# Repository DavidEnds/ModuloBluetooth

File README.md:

# ModuloBluetooth
This module enables any Arduino board to communicate data over Bluetooth. It's a great solution if you want to create wireless projects ranging from robots to living room lamps.

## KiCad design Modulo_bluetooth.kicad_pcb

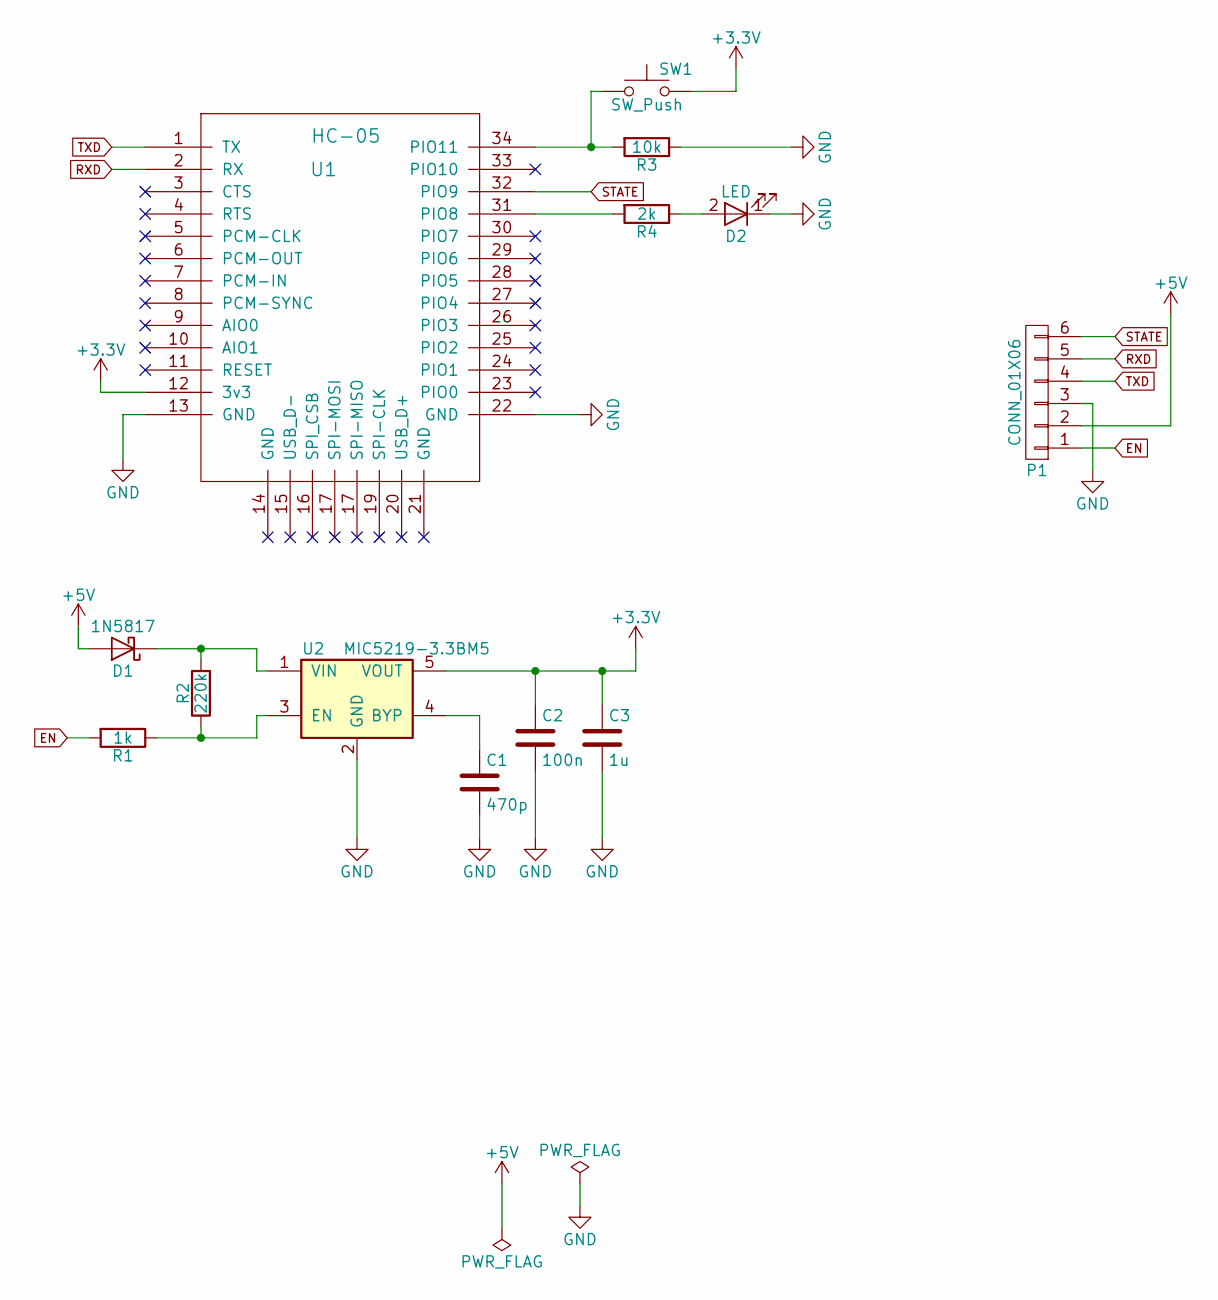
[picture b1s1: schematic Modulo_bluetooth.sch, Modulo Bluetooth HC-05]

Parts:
C1: 470p; C_0805_HandSoldering
C2: 100n; C_0805_HandSoldering
C3: 1u; C_0805_HandSoldering
D1: 1N5817; do214ac
D2: LED; LED_0805
P1: CONN_01X06; Pin_Header_Angled_1x06
R1: 1k; R_0805_HandSoldering
R2: 220k; R_0805_HandSoldering
R3: 10k; R_0805_HandSoldering
R4: 2k; R_0805_HandSoldering
SW1: SW_Push; SW_SPST_B3U-1000P-B
U1: HC-05; HC-06
U2: MIC5219-3.3BM5; SOT-23-5

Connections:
+3V3: C2.1, C3.1, SW1.2, U1.12 (3v3), U2.5 (VOUT)
+5V: D1.2 (A), P1.2
EN: P1.1, R1.2
GND: C1.2, C2.2, C3.2, D2.1 (K), P1.3, R3.1, U1.13 (GND), U1.22 (GND), U2.2 (GND)
unnamed: C1.1, U2.4 (BYP)
unnamed: D1.1 (K), R2.2, U2.1 (VIN)
unnamed: D2.2 (A), R4.1
unnamed: R1.1, R2.1, U2.3 (EN)
unnamed: R3.2, SW1.1, U1.34 (PIO11)
unnamed: R4.2, U1.31 (PIO8)
RXD: P1.5, U1.2 (RX)
STATE: P1.6, U1.32 (PIO9)
TXD: P1.4, U1.1 (TX)

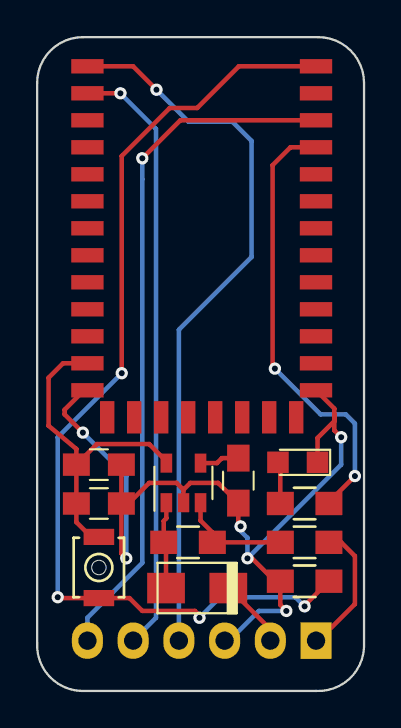
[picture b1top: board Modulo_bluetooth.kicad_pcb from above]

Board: 2 copper layers, 18.2 x 36.3 mm, 13 parts (0 on the bottom side), 13 nets.

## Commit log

2017-04-29 License Added
2017-04-29 Proyecto creado
2017-04-30 Esquematico en proceso
2017-04-30 Esquema terminado
2017-04-30 ERC pasado
2017-04-30 Layout terminado
2017-04-30 Serigrafia añadida
2017-06-05 Valor de R1 cambiado
2018-01-20 Gerbers exportado
    Gerbers exportados para prueba de panelizacion
2018-02-12 logo añadido
2018-02-24 logo cambiado
2018-03-04 arbol de carpetas cambiado
2018-05-06 BOM exportados
2018-05-06 gerbers generados
2018-05-14 Bom actualizado error en R1
2018-06-11 Datasheet subido
2018-07-14 re-rellenado el plano de masa
2018-07-15 Gerbers exportados
